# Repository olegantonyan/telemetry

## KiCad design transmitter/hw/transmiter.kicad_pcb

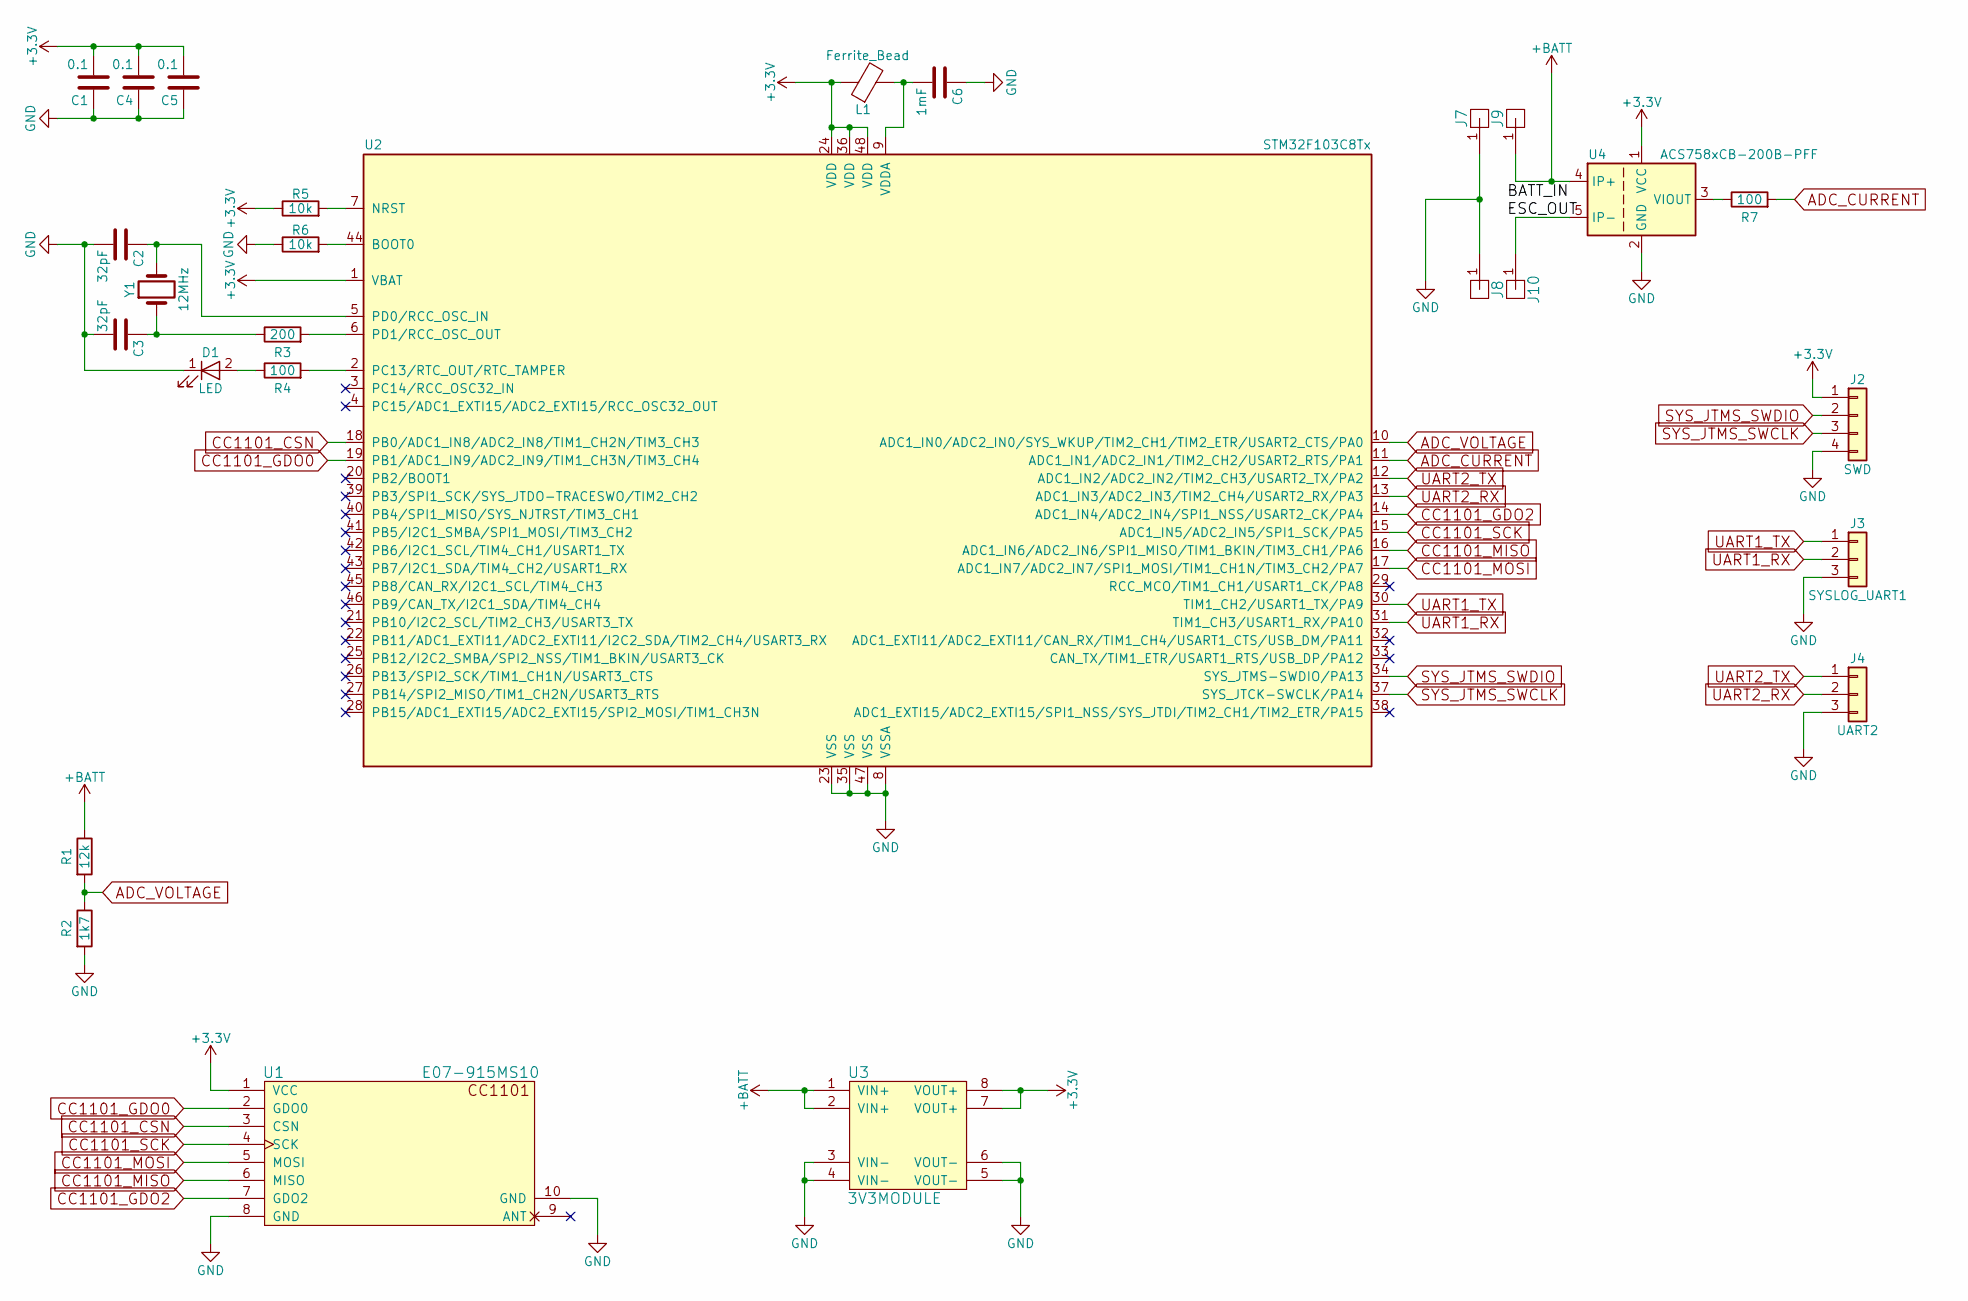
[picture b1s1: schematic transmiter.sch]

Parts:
C1, C4, C5: 0.1; C_0805_HandSoldering
C2, C3: 32pF; C_0805_HandSoldering
C6: 1mF; C_0805_HandSoldering
D1: LED; LED_0805_HandSoldering
J2: SWD; Pin_Header_Straight_1x04_Pitch2.54mm
J3: SYSLOG_UART1; Pin_Header_Straight_1x03_Pitch2.54mm
J4: UART2; Pin_Header_Straight_1x03_Pitch2.54mm
J7, J8, J9, J10: SolderPad; Solder_Terminal_Large
L1: Ferrite_Bead; L_0805_HandSoldering
R1: 12k; R_Axial_DIN0411_L9.9mm_D3.6mm_P12.70mm_Horizontal
R2: 1k7; R_Axial_DIN0411_L9.9mm_D3.6mm_P12.70mm_Horizontal
R3: 200; R_0805_HandSoldering
R4, R7: 100; R_0805_HandSoldering
R5, R6: 10k; R_0805_HandSoldering
U1: E07-915MS10; E07-915MS10 module
U2: STM32F103C8Tx; LQFP-48_7x7mm_Pitch0.5mm
U3: 3V3MODULE
U4: ACS758xCB-200B-PFF; Allegro_CB_PFF
Y1: 12MHz; Crystal_SMD_HC49-SD_HandSoldering

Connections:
+3V3: C1.2, C4.2, C5.2, J2.1, L1.1, R5.1, U1.1 (VCC), U2.1 (VBAT), U2.24 (VDD), U2.36 (VDD), U2.48 (VDD), U3.7 (VOUT+), U3.8 (VOUT+), U4.1 (VCC)
+BATT: J9.1, R1.1, U3.1 (VIN+), U3.2 (VIN+), U4.4 (IP+)
ADC_CURRENT: R7.2, U2.11 (ADC1_IN1/ADC2_IN1/TIM2_CH2/USART2_RTS/P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)
ADC_VOLTAGE: R1.2, R2.1, U2.10 (ADC1_IN0/ADC2_IN0/SYS_WKUP/TIM2_CH1/TIM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)
CC1101_CSN: U1.3 (CSN), U2.18 (PB0/ADC1_IN8/ADC2_IN8/TIM1_CH2N/TIM3_CH3)
CC1101_GDO0: U1.2 (GDO0), U2.19 (PB1/ADC1_IN9/ADC2_IN9/TIM1_CH3N/TIM3_CH4)
CC1101_GDO2: U1.7 (GDO2), U2.14 (ADC1_IN4/ADC2_IN4/SPI1_NSS/USART2_CK/PA4)
CC1101_MISO: U1.6 (MISO), U2.16 (ADC1_IN6/ADC2_IN6/SPI1_MISO/TIM1_BKIN/T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)
CC1101_MOSI: U1.5 (MOSI), U2.17 (ADC1_IN7/ADC2_IN7/SPI1_MOSI/TIM1_CH1N/T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)
CC1101_SCK: U1.4 (SCK), U2.15 (ADC1_IN5/ADC2_IN5/SPI1_SCK/PA5)
GND: C1.1, C2.2, C3.2, C4.1, C5.1, C6.1, D1.1 (K), J2.4, J3.3, J4.3, J7.1, J8.1, R2.2, R6.1, U1.8 (GND), U1.10 (GND), U2.8 (VSSA), U2.23 (VSS), U2.35 (VSS), U2.47 (VSS), U3.3 (VIN-), U3.4 (VIN-), U3.5 (VOUT-), U3.6 (VOUT-), U4.2 (GND)
unnamed: C2.1, U2.5 (PD0/RCC_OSC_IN), Y1.2
unnamed: C3.1, R3.1, Y1.1
unnamed: C6.2, L1.2, U2.9 (VDDA)
unnamed: D1.2 (A), R4.1
unnamed: J10.1, U4.5 (IP-)
unnamed: R3.2, U2.6 (PD1/RCC_OSC_OUT)
unnamed: R4.2, U2.2 (PC13/RTC_OUT/RTC_TAMPER)
unnamed: R5.2, U2.7 (NRST)
unnamed: R6.2, U2.44 (BOOT0)
unnamed: R7.1, U4.3 (VIOUT)
SYS_JTMS_SWCLK: J2.3, U2.37 (SYS_JTCK-SWCLK/PA14)
SYS_JTMS_SWDIO: J2.2, U2.34 (SYS_JTMS-SWDIO/PA13)
UART1_RX: J3.2, U2.31 (TIM1_CH3/USART1_RX/PA10)
UART1_TX: J3.1, U2.30 (TIM1_CH2/USART1_TX/PA9)
UART2_RX: J4.2, U2.13 (ADC1_IN3/ADC2_IN3/TIM2_CH4/USART2_RX/PA3)
UART2_TX: J4.1, U2.12 (ADC1_IN2/ADC2_IN2/TIM2_CH3/USART2_TX/PA2)

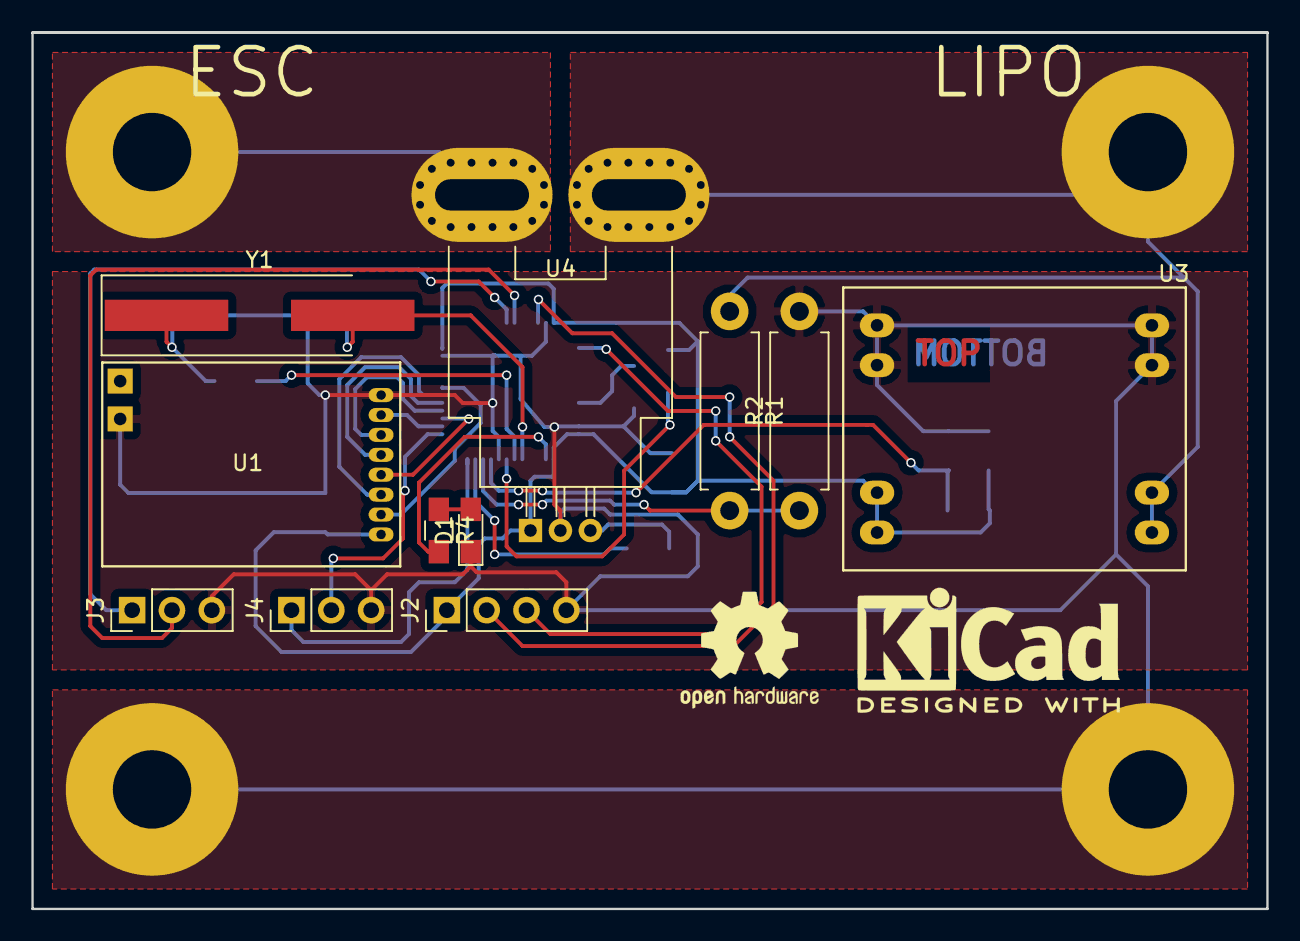
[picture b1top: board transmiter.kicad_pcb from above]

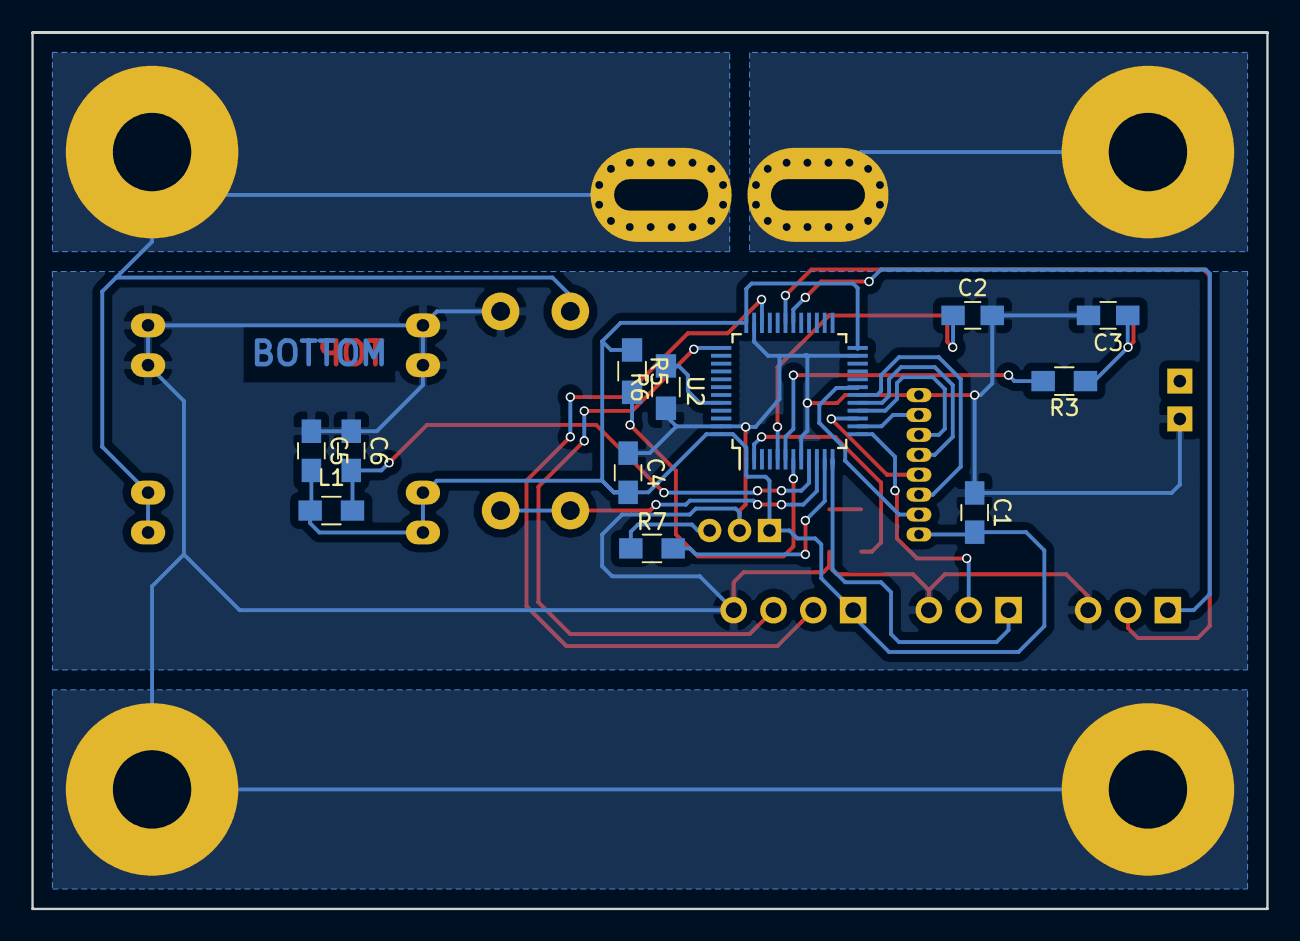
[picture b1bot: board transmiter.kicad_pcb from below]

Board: 2 copper layers, 78.7 x 55.9 mm, 27 parts (12 on the bottom side), 27 nets.

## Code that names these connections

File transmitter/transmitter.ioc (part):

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Mcu.Name=STM32F103C(8-B)Tx
Mcu.Package=LQFP48
Mcu.UserName=STM32F103C8Tx
PA0-WKUP.GPIOParameters=GPIO_Label
PA0-WKUP.GPIO_Label=ADC VOLTAGE
PA0-WKUP.Signal=ADCx_IN0
PA1.GPIOParameters=GPIO_Label
PA1.GPIO_Label=ADC_CURRENT
PA1.Signal=ADCx_IN1
PA10.Mode=Asynchronous
PA10.Signal=USART1_RX
PA13.Mode=Serial_Wire
PA13.Signal=SYS_JTMS-SWDIO
PA14.Mode=Serial_Wire
PA14.Signal=SYS_JTCK-SWCLK
PA2.Mode=Asynchronous
PA2.Signal=USART2_TX
PA3.Mode=Asynchronous
PA3.Signal=USART2_RX
PA4.GPIOParameters=GPIO_Label
PA4.GPIO_Label=CC1101 GDO2
PA4.Signal=GPIO_Input
PA5.GPIOParameters=GPIO_Label
PA5.GPIO_Label=CC1101 SCK
PA5.Mode=Full_Duplex_Master
PA5.Signal=SPI1_SCK
PA6.GPIOParameters=GPIO_Label
PA6.GPIO_Label=CC1101 MISO
PA6.Mode=Full_Duplex_Master
PA6.Signal=SPI1_MISO
PA7.GPIOParameters=GPIO_Label
PA7.GPIO_Label=CC1101 MOSI
PA7.Mode=Full_Duplex_Master
PA7.Signal=SPI1_MOSI
PA9.Mode=Asynchronous
PA9.Signal=USART1_TX
PB0.GPIOParameters=GPIO_Label
PB0.GPIO_Label=CC1101_CSN
PB0.Signal=GPIO_Output
PB1.GPIOParameters=GPIO_Label,GPIO_ModeDefaultEXTI
PB1.GPIO_Label=CC1101_GDO0
PB1.GPIO_ModeDefaultEXTI=GPIO_MODE_IT_FALLING
PB1.Signal=GPXTI1
PC13-TAMPER-RTC.GPIOParameters=GPIO_Label
PC13-TAMPER-RTC.GPIO_Label=RED LED
PC13-TAMPER-RTC.Signal=GPIO_Output
PD0-OSC_IN.Signal=RCC_OSC_IN
PD1-OSC_OUT.Signal=RCC_OSC_OUT
RCC.SYSCLKFreq_VALUE=24000000
RCC.SYSCLKSource=RCC_SYSCLKSOURCE_PLLCLK
board=transmitter

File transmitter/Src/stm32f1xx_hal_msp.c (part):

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    __HAL_RCC_ADC1_CLK_ENABLE();
  
    /**ADC1 GPIO Configuration    
    PA0-WKUP     ------> ADC1_IN0
    PA1     ------> ADC1_IN1 
    */
    GPIO_InitStruct.Pin = ADC_VOLTAGE_Pin|ADC_CURRENT_Pin;
    GPIO_InitStruct.Mode = GPIO_MODE_ANALOG;
    HAL_GPIO_Init(GPIOA, &GPIO_InitStruct);

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    __HAL_RCC_ADC1_CLK_DISABLE();
  
    /**ADC1 GPIO Configuration    
    PA0-WKUP     ------> ADC1_IN0
    PA1     ------> ADC1_IN1 
    */
    HAL_GPIO_DeInit(GPIOA, ADC_VOLTAGE_Pin|ADC_CURRENT_Pin);

    /* ADC1 DMA DeInit */
    HAL_DMA_DeInit(hadc->DMA_Handle);
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    __HAL_RCC_SPI1_CLK_ENABLE();
  
    /**SPI1 GPIO Configuration    
    PA5     ------> SPI1_SCK
    PA6     ------> SPI1_MISO
    PA7     ------> SPI1_MOSI 
    */
    GPIO_InitStruct.Pin = CC1101_SCK_Pin|CC1101_MOSI_Pin;
    GPIO_InitStruct.Mode = GPIO_MODE_AF_PP;
    GPIO_InitStruct.Speed = GPIO_SPEED_FREQ_HIGH;
    HAL_GPIO_Init(GPIOA, &GPIO_InitStruct);

    GPIO_InitStruct.Pin = CC1101_MISO_Pin;
    GPIO_InitStruct.Mode = GPIO_MODE_INPUT;
    GPIO_InitStruct.Pull = GPIO_NOPULL;
    HAL_GPIO_Init(CC1101_MISO_GPIO_Port, &GPIO_InitStruct);

  /* USER CODE BEGIN SPI1_MspInit 1 */

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    __HAL_RCC_SPI1_CLK_DISABLE();
  
    /**SPI1 GPIO Configuration    
    PA5     ------> SPI1_SCK
    PA6     ------> SPI1_MISO
    PA7     ------> SPI1_MOSI 
    */
    HAL_GPIO_DeInit(GPIOA, CC1101_SCK_Pin|CC1101_MISO_Pin|CC1101_MOSI_Pin);

  /* USER CODE BEGIN SPI1_MspDeInit 1 */

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    __HAL_RCC_USART1_CLK_ENABLE();
  
    /**USART1 GPIO Configuration    
    PA9     ------> USART1_TX
    PA10     ------> USART1_RX 
    */
    GPIO_InitStruct.Pin = GPIO_PIN_9;
    GPIO_InitStruct.Mode = GPIO_MODE_AF_PP;
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    __HAL_RCC_USART2_CLK_ENABLE();
  
    /**USART2 GPIO Configuration    
    PA2     ------> USART2_TX
    PA3     ------> USART2_RX 
    */
    GPIO_InitStruct.Pin = GPIO_PIN_2;
    GPIO_InitStruct.Mode = GPIO_MODE_AF_PP;
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    __HAL_RCC_USART1_CLK_DISABLE();
  
    /**USART1 GPIO Configuration    
    PA9     ------> USART1_TX
    PA10     ------> USART1_RX 
    */
    HAL_GPIO_DeInit(GPIOA, GPIO_PIN_9|GPIO_PIN_10);

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    __HAL_RCC_USART2_CLK_DISABLE();
  
    /**USART2 GPIO Configuration    
    PA2     ------> USART2_TX
    PA3     ------> USART2_RX 
    */
    HAL_GPIO_DeInit(GPIOA, GPIO_PIN_2|GPIO_PIN_3);

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
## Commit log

2017-06-13 initial; docs, stubs, etc
2017-06-14 transmitter skeleton project for stm32 makefile
2017-06-15 blink led
2017-06-15 stm32cubemx update
2017-06-17 checkpoint
2017-06-17 adc with dma
2017-06-17 adc with dma checkpoint
2017-06-17 extract adc app to subdir
2017-06-18 adc printf average voltage
2017-06-18 reduce adc sampling rate
2017-06-18 serial log thread
2017-06-20 receiver stub project
2017-06-22 rf added
2017-06-24 rf debugging
2017-06-24 moving code around; playing with receiver
2017-06-26 added code samples to docs; moving code around
2017-07-18 si4463 driver added to transmitter
2017-07-19 refactor rf
2017-07-20 remove delays
2017-07-20 updated cubemx; enabled watchdog
2017-07-21 receiver works with queue
2017-07-21 add mutex for buffer read
2017-07-21 si4463 driver in shared folder
2017-07-21 tx semaphore
2017-07-21 leds
2017-07-22 printf to uart1
2017-07-22 12 byte packet with crc
2017-07-22 12 bytes no crc
2017-07-22 move rf to shared
2017-07-22 crc calculation in stm32
2017-07-23 enable i2c for oled in receiver
2017-07-24 fix crc calc
2017-07-24 16 packet length
2017-07-24 sh1106 display driver prototype
2017-07-24 move rf_packet_length define
2017-07-24 rf merge back master
2017-07-24 sh1106 datasheet added
2017-07-25 added gui thread
2017-07-25 i2c fast mode
2017-07-25 render function calls wadchdog kick
2017-07-25 u8g2 another try
2017-07-25 u8g2 remove; no luck
2017-07-26 fonts begin
2017-07-27 fonts: 4 and 5
2017-07-28 fonts: 6 and 7
2017-07-28 display voltage
2017-07-28 increase spacing after dot
2017-07-29 driver updated
2017-07-29 si5563 crc finally!
2017-07-29 20k 2gfsk rate
2017-07-29 2fsk 30k deviation
2017-07-29 433mhz instead of 435 seems to be better
2017-07-29 buzzer added
2017-07-30 buzzer works
2017-08-04 prepare for current
2017-08-04 wdt in idle hook; measure current stub
2017-08-04 i2c transmit with dma and interrupts - possibly fix watchdog issue
2017-09-07 prepare cc1101
2017-09-08 cc1101 driver stub; it compiles
2017-09-08 syslog
2017-09-08 syslog shared; pin remap
2017-09-09 read cc1101 version works
2017-09-09 more docs
2018-01-18 Makefile update - new toolchain
2018-01-22 tx command
2018-01-24 update cubemx; checkpoint
2018-01-25 cc1101 almost works
2018-01-25 cc1101 minor changes
2018-01-25 cc1101 use dynamic memory for rx
2018-01-25 cleanup
2018-01-25 whitening + max power
2018-01-25 replace defines with enums
2018-01-27 disable watchdog for testing
2018-01-27 update cubemx
2018-01-29 enable watchdog back; prevent cc1101 interrupt handling before initialization
2018-01-29 smartrf config in project
2018-02-03 fix cc1101 interrupt state machine; work at higher baudrate
2018-02-03 cc1101 always start rx in interrupt if anything wrong with fifo
2018-02-04 cc1101 wait for tx finished after starting
2018-02-15 kicad files for transmitter; cleanup
2018-02-15 kicad files and cleanup
2018-03-22 transmitter uses internal oscillator
2018-09-22 transmitter schematic update
2018-09-23 delay before display init
2018-09-23 ADC voltage div fix; schematic
2018-09-25 ADC sample rate change

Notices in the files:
transmitter/Src/stm32f1xx_hal_msp.c:
Copyright (c) 2018 STMicroelectronics International N.V.
All rights reserved.
(C) COPYRIGHT STMicroelectronics *****END OF FILE
